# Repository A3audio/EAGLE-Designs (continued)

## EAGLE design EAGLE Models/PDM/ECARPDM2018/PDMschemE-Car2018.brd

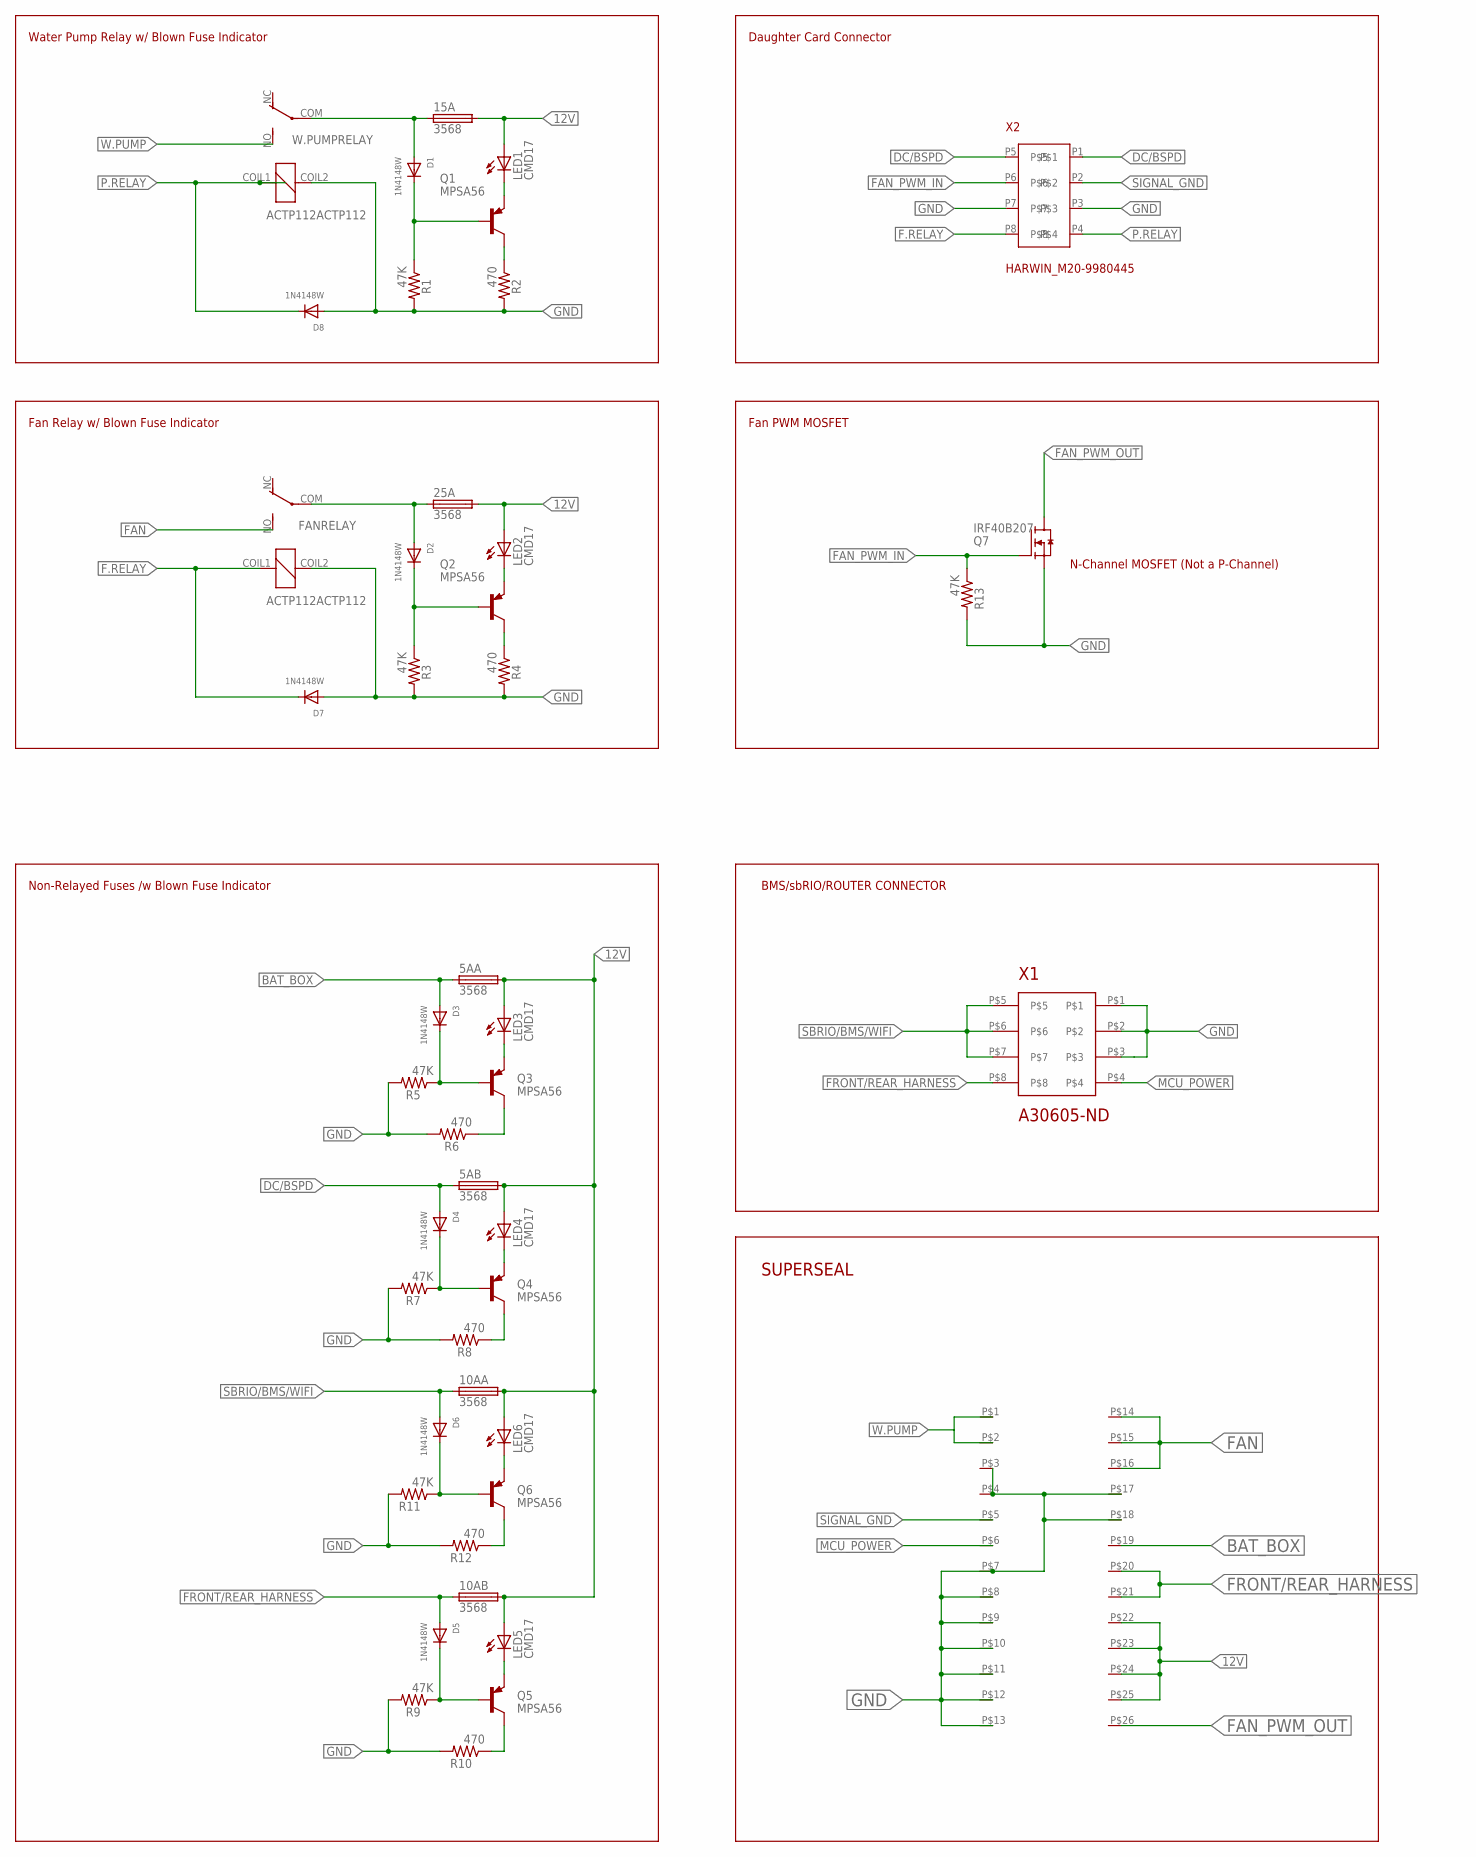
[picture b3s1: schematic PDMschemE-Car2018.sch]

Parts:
5AA, 5AB, 10AA, 10AB, 15A, 25A: 3568
D1, D2, D3, D4, D5, D6, D7, D8: 1N4148W; SOD-123
FANRELAY: ACTP112ACTP112; ACTP112
LED1, LED2, LED3, LED4, LED5, LED6: CMD17; CHIPLED_0805
Q1, Q2, Q3, Q4, Q5, Q6: MPSA56; TO92-CBE
Q7: IRF40B207; TO220-3
R1, R3, R5, R7, R9, R11, R13: 47K; R1206
R2, R4, R6, R8, R10, R12: 470; R1206
U$4: SUPERSEAL1.0_26POS_2ROW
W.PUMPRELAY: ACTP112ACTP112; ACTP112
X1: A30605-ND
X2: HARWIN_M20-9980445

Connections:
12V: 5AA.3 (2), 5AA.4 (2), 5AB.3 (2), 5AB.4 (2), 10AA.3 (2), 10AA.4 (2), 10AB.3 (2), 10AB.4 (2), 15A.3 (2), 15A.4 (2), 25A.3 (2), 25A.4 (2), LED1.A, LED2.A, LED3.A, LED4.A, LED5.A, LED6.A, U$4.P$22 (B22), U$4.P$23 (B23), U$4.P$24 (B24), U$4.P$25 (B25)
BAT_BOX: 5AA.1, 5AA.2 (1), D3.A, U$4.P$19 (B19)
DC/BSPD: 5AB.1, 5AB.2 (1), D4.A, X2.P1, X2.P5
F.RELAY: D7.C, FANRELAY.COIL1, X2.P8
FAN: FANRELAY.NO, U$4.P$14 (B14), U$4.P$15 (B15), U$4.P$16 (B16)
FAN_PWM_IN: Q7.G, R13.1, X2.P6
FAN_PWM_OUT: Q7.D, U$4.P$26 (B26)
FRONT/REAR_HARNESS: 10AB.1, 10AB.2 (1), D5.A, U$4.P$20 (B20), U$4.P$21 (B21), X1.P$8
GND: D7.A, D8.A, FANRELAY.COIL2, Q7.S, R1.2, R2.2, R3.2, R4.2, R5.2, R6.2, R7.2, R8.2, R9.2, R10.2, R11.2, R12.2, R13.2, U$4.P$3 (B3), U$4.P$4 (B4), U$4.P$7 (B7), U$4.P$8 (B8), U$4.P$9 (B9), U$4.P$10 (B10), U$4.P$11 (B11), U$4.P$12 (B12), U$4.P$13 (B13), U$4.P$17 (B17), U$4.P$18 (B18), W.PUMPRELAY.COIL2, X1.P$1, X1.P$2, X1.P$3, X2.P3, X2.P7
MCU_POWER: U$4.P$6 (B6), X1.P$4
unnamed: LED1.C, Q1.E
unnamed: Q3.C, R6.1
unnamed: LED3.C, Q3.E
unnamed: 25A.1, 25A.2 (1), D2.A, FANRELAY.COM
unnamed: Q1.C, R2.1
unnamed: D1.C, Q1.B, R1.1
unnamed: D2.C, Q2.B, R3.1
unnamed: 15A.1, 15A.2 (1), D1.A, W.PUMPRELAY.COM
unnamed: Q2.C, R4.1
unnamed: LED2.C, Q2.E
unnamed: D3.C, Q3.B, R5.1
unnamed: LED4.C, Q4.E
unnamed: D4.C, Q4.B, R7.1
unnamed: Q4.C, R8.1
unnamed: LED6.C, Q6.E
unnamed: D6.C, Q6.B, R11.1
unnamed: Q6.C, R12.1
unnamed: LED5.C, Q5.E
unnamed: D5.C, Q5.B, R9.1
unnamed: Q5.C, R10.1
P.RELAY: D8.C, W.PUMPRELAY.COIL1, X2.P4
SBRIO/BMS/WIFI: 10AA.1, 10AA.2 (1), D6.A, X1.P$5, X1.P$6, X1.P$7
SIGNAL_GND: U$4.P$5 (B5), X2.P2
W.PUMP: U$4.P$1 (B1), U$4.P$2 (B2), W.PUMPRELAY.NO

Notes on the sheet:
Water Pump Relay w/ Blown Fuse Indicator
Fan Relay w/ Blown Fuse Indicator
Non-Relayed Fuses /w Blown Fuse Indicator
Fan PWM MOSFET
N-Channel MOSFET (Not a P-Channel)
Daughter Card Connector
BMS/sbRIO/ROUTER CONNECTOR
SUPERSEAL

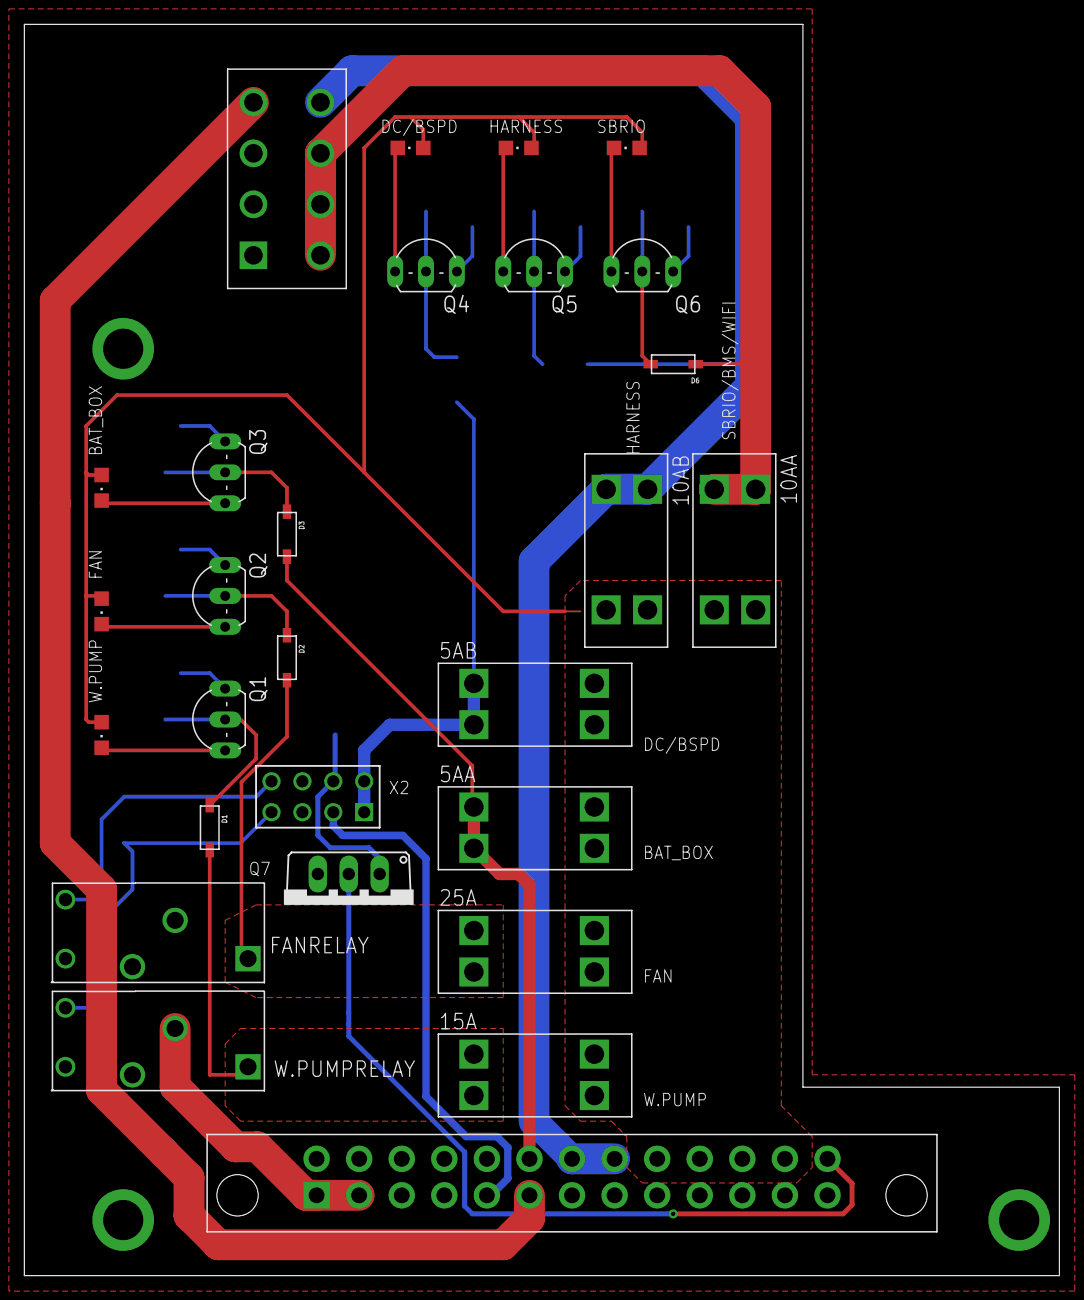
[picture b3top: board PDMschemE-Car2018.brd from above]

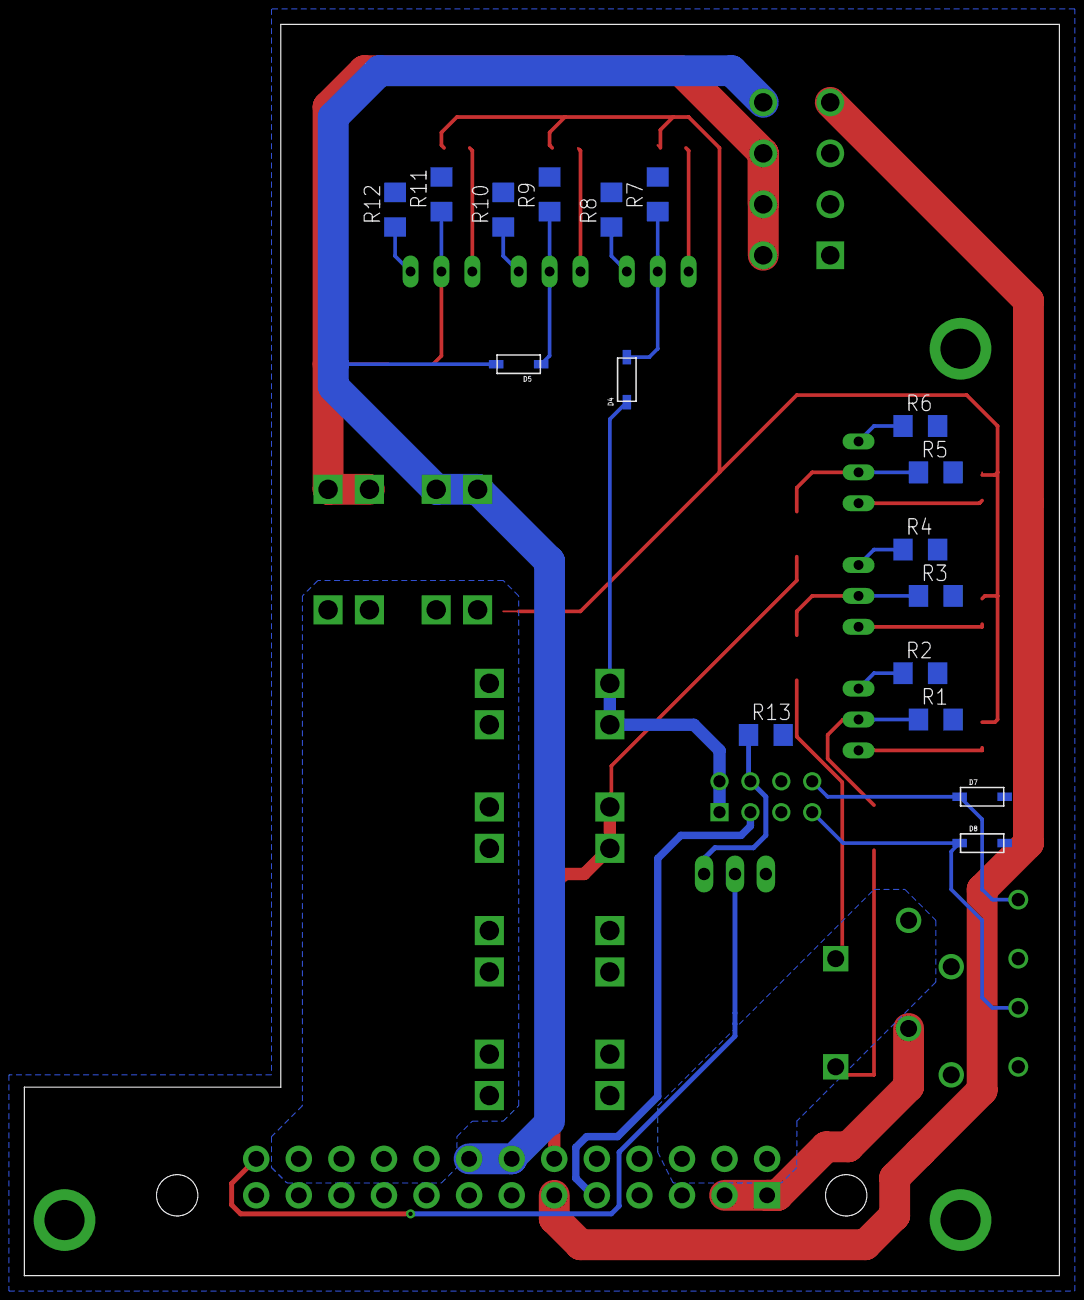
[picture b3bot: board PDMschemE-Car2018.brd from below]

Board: 2 copper layers, 85.1 x 102.9 mm, 45 parts (17 on the bottom side), 34 nets.

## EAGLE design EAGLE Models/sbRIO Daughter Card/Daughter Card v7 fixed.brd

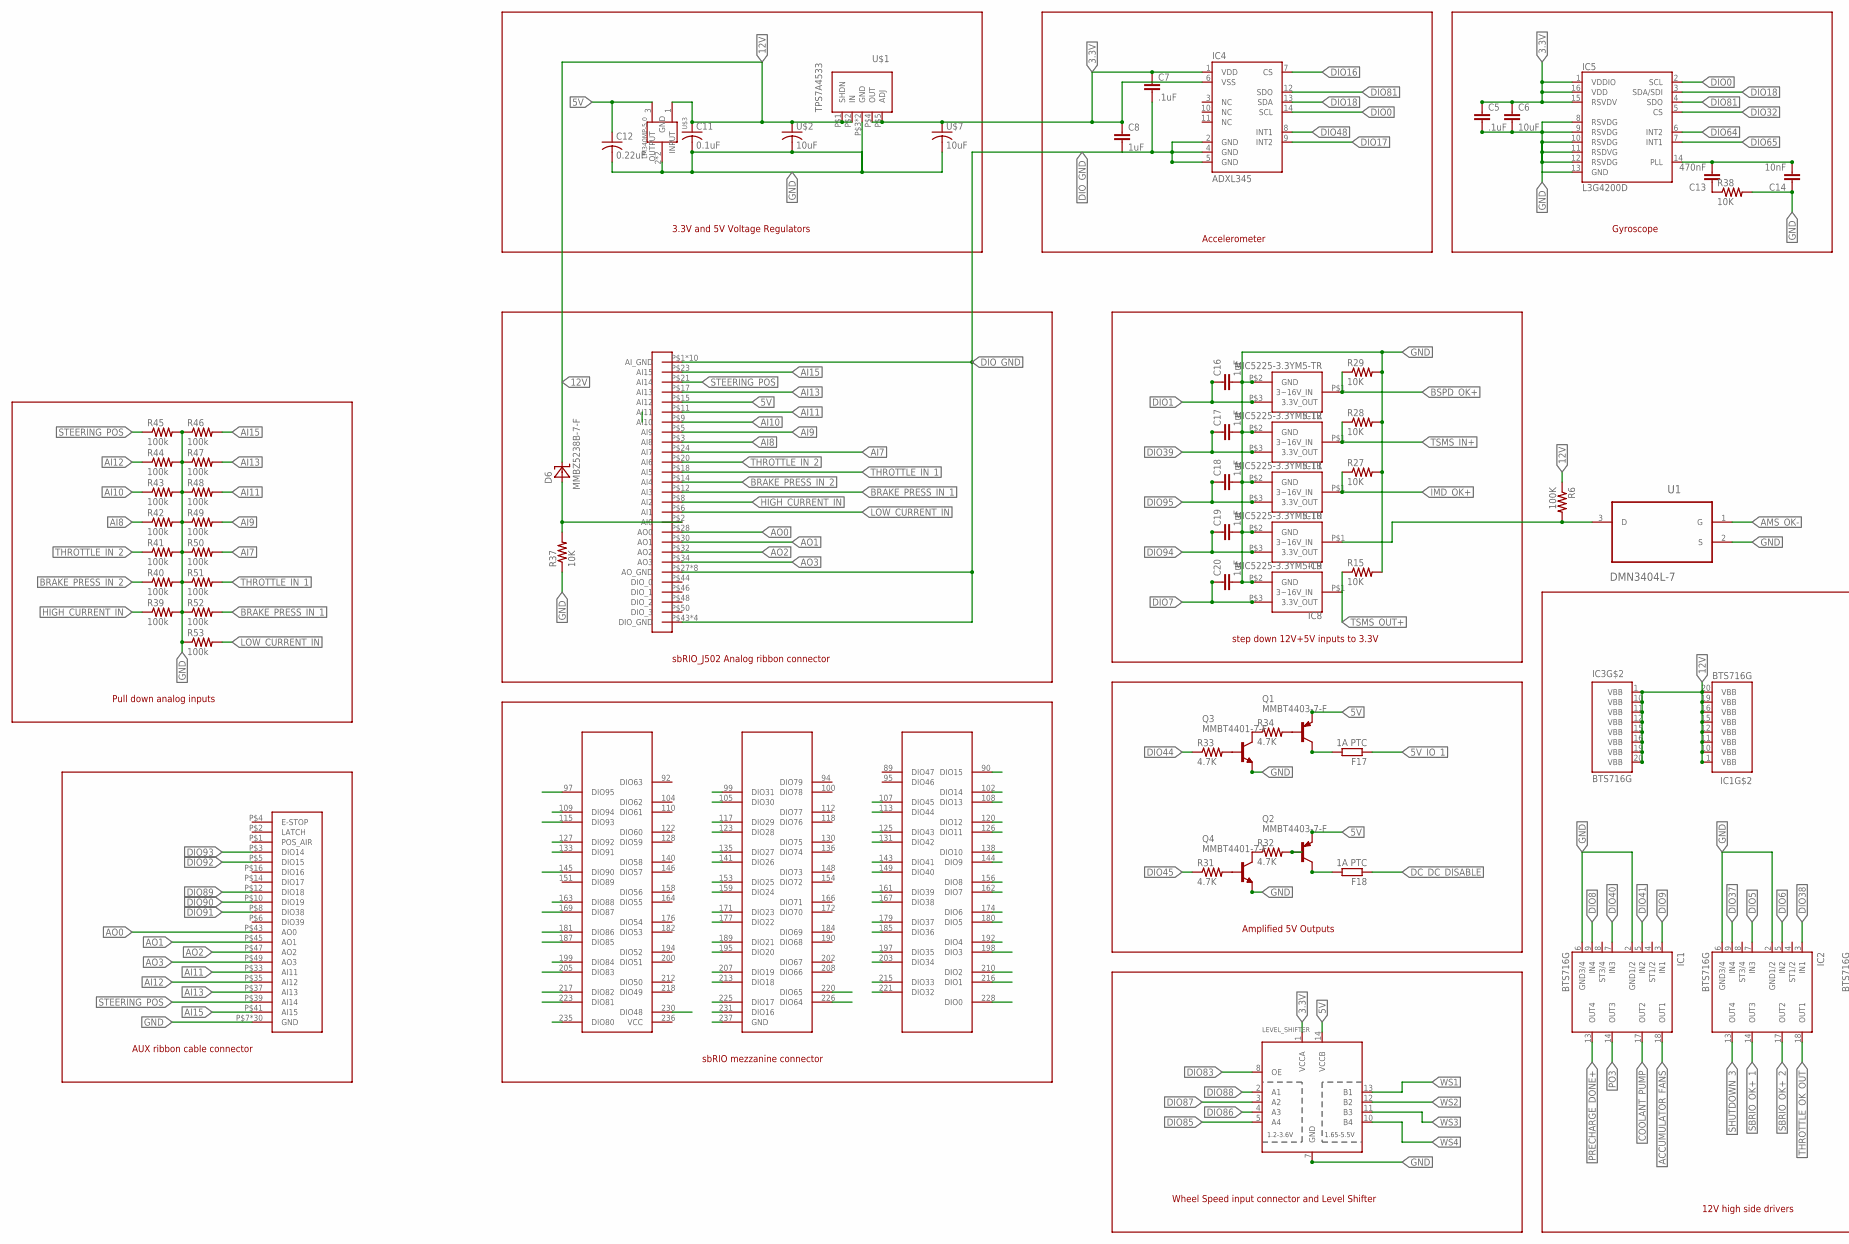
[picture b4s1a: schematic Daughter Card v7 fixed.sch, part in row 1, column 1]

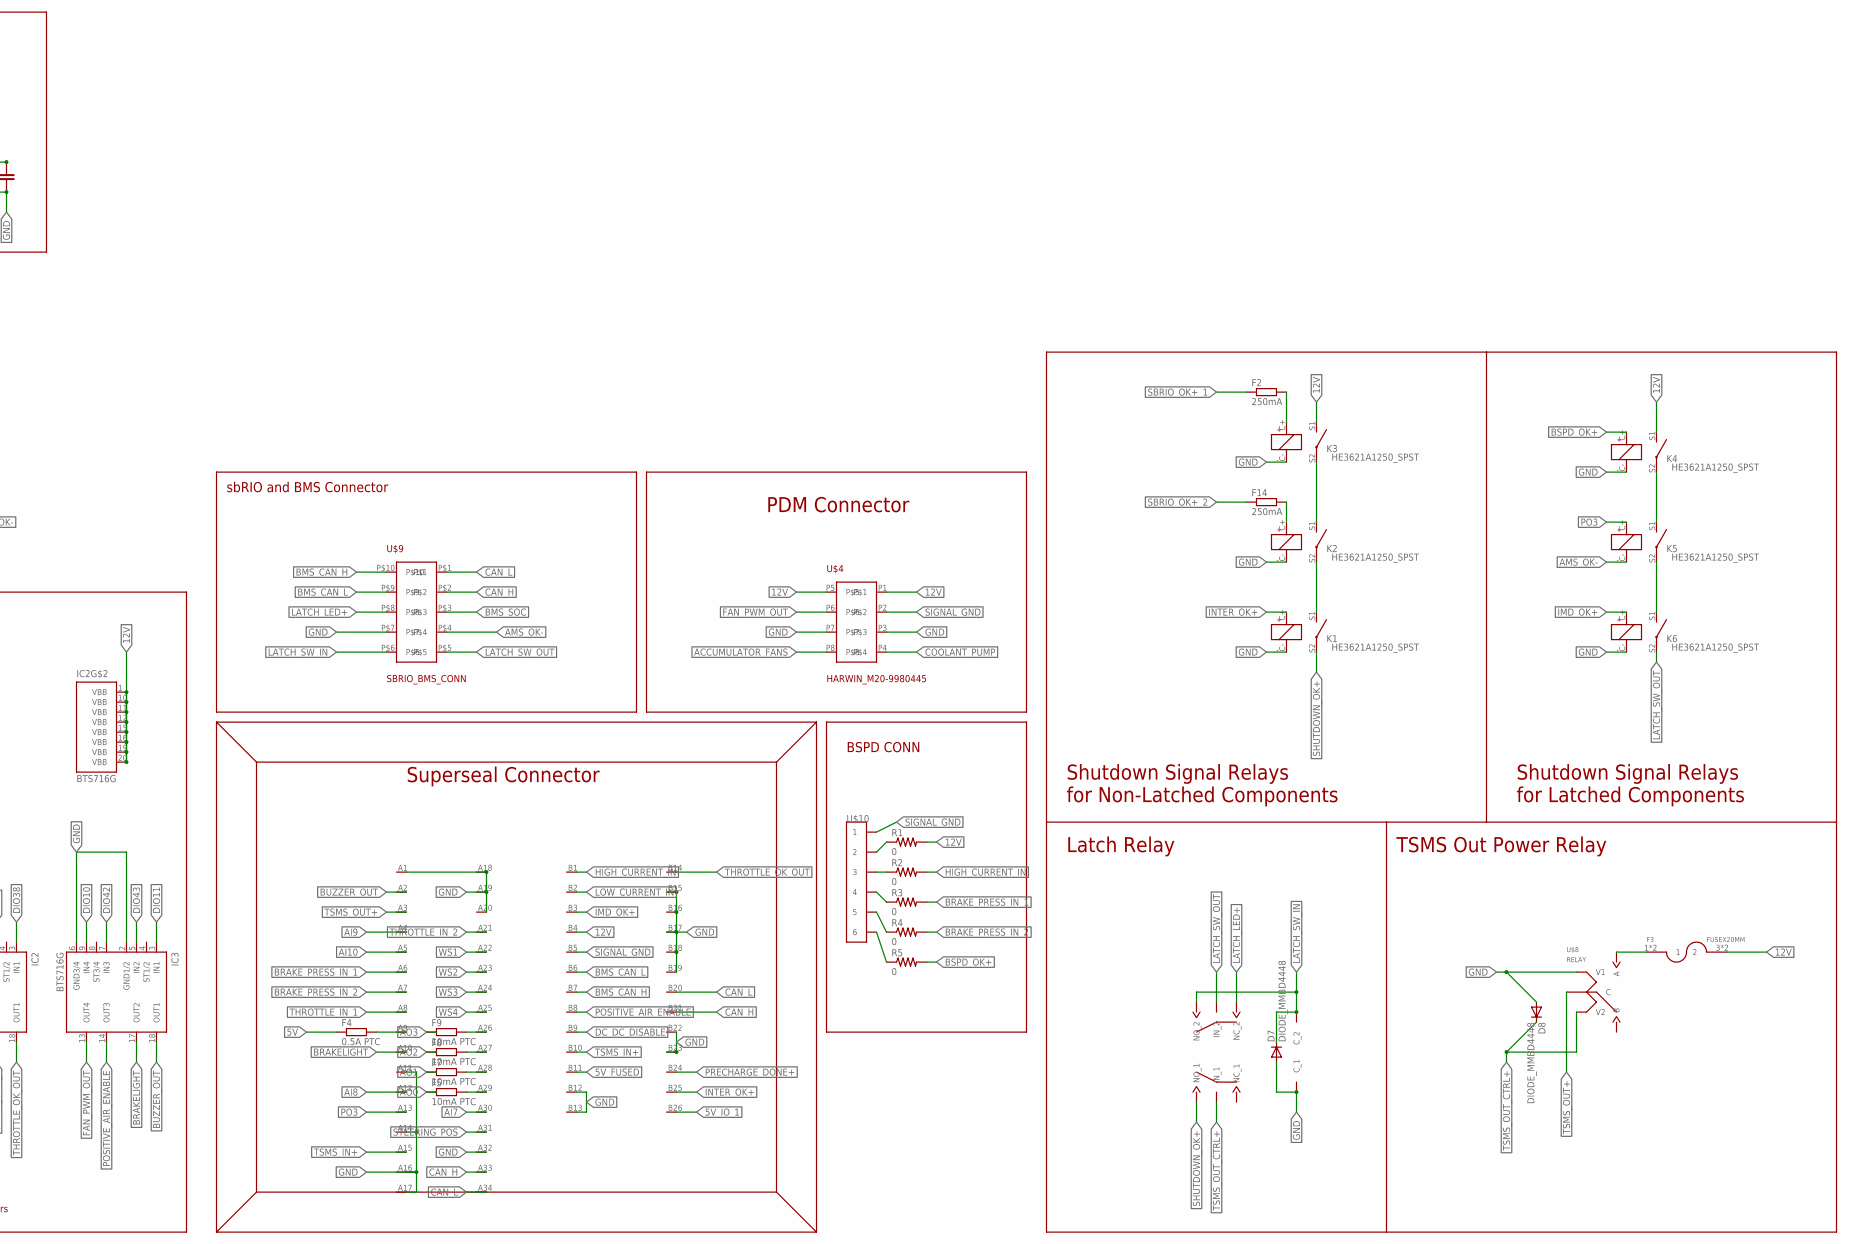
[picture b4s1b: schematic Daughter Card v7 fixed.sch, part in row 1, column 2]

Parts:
C5, C7: .1uF; 0603-CAP
C6: 10uF; 0603-CAP
C8, C16, C17, C18, C19, C20: 1uF; 0603-CAP
C11: 0.1uF; C1206
C12: 0.22uF; C1206
C13: 470nF; 0603-CAP
C14: 10nF; 0603-CAP
D6: MMBZ5238B-7-F; SOT-23-3
D7, D8: DIODE_MMBD4448; SOT-23-3
F2, F14: 250mA; R0603
F3: FUSEX20MM; FUSE_5MM
F4: 0.5A PTC; R0603
F5, F7, F8, F9: 10mA PTC; R0603
F17, F18: 1A PTC; R0603
IC1, IC2, IC3: BTS716G; PG-DSO-20
IC4: ADXL345; LGA14
IC5: L3G4200D; LGA16-4X4
IC8, IC9, IC10, IC11, IC12: MIC5225-3.3YM5-TR; SOT-23-3
K1, K2, K3, K4, K5, K6: HE3621A1250_SPST
LATCH_U7: JW2SN-DC12V; DPDT_JW2_FORM_C
LEVEL_SHIFTER: TXB0104PWR; TSSOP14
Q1, Q2: MMBT4403-7-F; SOT-23-3
Q3, Q4: MMBT4401-7-F; SOT-23-3
R1, R2, R3, R4, R5: 0; M0805
R6: 100K; R0603
R15, R27, R28, R29, R37, R38: 10K; R0603
R31, R32, R33, R34: 4.7K; R0603
R39, R40, R41, R42, R43, R44, R45, R46, R47, R48, R49, R50, R51, R52, R53: 100k; R0603
SBRIO_ANALOG: SBRIO_MIO; SBRIO_J502_J503
SBRIO_AUX: SBRIO_AUX; SBRIO_J502_J503
SBRIO_MEZZANINE: SBRIO_RMC; SEAM-40-XX.X-XX-06-X-A
U1: DMN3404L-7; SOT95P235X112-3N
U$1: TPS7A4533; DIGIKEY_P-N 490-12344-1-ND
U$2, U$7: 10uF; C1206
U$3: LM340MP-5.0; SOT-223-4
U$4: HARWIN_M20-9980445
U$6: SUPERSEAL1.0_60POS
U$8: RELAY
U$9: SBRIO_BMS_CONN; SBRIO_W
U$10: SULLINS_1MM_6P_HEADER; SULLINS_1MM_HEADER

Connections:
3.3V: C5.1, C6.1, C7.1, C8.1, IC4.1 (VDD), IC4.6 (VSS), IC5.1 (VDDIO), IC5.15 (RSVDV), IC5.16 (VDD), LEVEL_SHIFTER.1 (VCCA), U$1.P$4 (OUT), U$1.P$5 (ADJ), U$7.1
5V: C12.1, F4.1, LEVEL_SHIFTER.14 (VCCB), Q1.P$3 (E), Q2.P$3 (E), SBRIO_ANALOG.P$15 (AI12), U$3.3 (OUTPUT)
5V_FUSED: F4.2, U$6.A9, U$6.B11
5V_IO_1: F17.1, U$6.B26
12V: C11.1, D6.P$1 (C), F3.3 (2), F3.4 (2), IC1.1 (VBB), IC1.10 (VBB), IC1.11 (VBB), IC1.12 (VBB), IC1.15 (VBB), IC1.16 (VBB), IC1.19 (VBB), IC1.20 (VBB), IC2.1 (VBB), IC2.10 (VBB), IC2.11 (VBB), IC2.12 (VBB), IC2.15 (VBB), IC2.16 (VBB), IC2.19 (VBB), IC2.20 (VBB), IC3.1 (VBB), IC3.10 (VBB), IC3.11 (VBB), IC3.12 (VBB), IC3.15 (VBB), IC3.16 (VBB), IC3.19 (VBB), IC3.20 (VBB), K3.S1 (SW_1), K4.S1 (SW_1), R1.2, R6.1, U$1.P$1 (SHDN), U$1.P$2 (IN), U$2.1, U$3.1 (INPUT), U$4.P1, U$4.P5, U$6.B4
ACCUMULATOR_FANS: IC1.18 (OUT1), U$4.P8
AI7: R50.2, SBRIO_ANALOG.P$24 (AI7), U$6.A30
AI8: R42.1, SBRIO_ANALOG.P$3 (AI8), U$6.A12
AI9: R49.2, SBRIO_ANALOG.P$5 (AI9), U$6.A4
AI10: R43.1, SBRIO_ANALOG.P$9 (AI10), U$6.A5
AI11: R48.2, SBRIO_ANALOG.P$11 (AI11), SBRIO_AUX.P$33 (AI11)
AI12: R44.1, SBRIO_AUX.P$35 (AI12)
AI13: R47.2, SBRIO_ANALOG.P$17 (AI13), SBRIO_AUX.P$37 (AI13)
AI15: R46.2, SBRIO_ANALOG.P$23 (AI15), SBRIO_AUX.P$41 (AI15)
AMS_OK-: K5.C-, U1.1 (G), U$9.P$4
AO0: F5.1, SBRIO_ANALOG.P$28 (AO0), SBRIO_AUX.P$43 (AO0)
AO1: F7.1, SBRIO_ANALOG.P$30 (AO1), SBRIO_AUX.P$45 (AO1)
AO2: F8.1, SBRIO_ANALOG.P$32 (AO2), SBRIO_AUX.P$47 (AO2)
AO3: F9.1, SBRIO_ANALOG.P$34 (AO3), SBRIO_AUX.P$49 (AO3)
BMS_CAN_H: U$6.B7, U$9.P$10
BMS_CAN_L: U$6.B6, U$9.P$9
BMS_SOC: U$9.P$3
BRAKELIGHT: IC3.17 (OUT2), U$6.A10
BRAKE_PRESS_IN_1: R3.2, R52.2, SBRIO_ANALOG.P$12 (AI3), U$6.A6
BRAKE_PRESS_IN_2: R4.2, R40.1, SBRIO_ANALOG.P$14 (AI4), U$6.A7
BSPD_OK+: IC12.P$1 (3~16V_IN), K4.C+, R5.2, R29.1
BUZZER_OUT: IC3.18 (OUT1), U$6.A2
CAN_H: U$6.A33, U$6.B21, U$9.P$2
CAN_L: U$6.A34, U$6.B20, U$9.P$1
COOLANT_PUMP: IC1.17 (OUT2), U$4.P4
DC_DC_DISABLE: F18.1, U$6.B9
DIO0: IC4.14 (SCL), IC5.2 (SCL), SBRIO_MEZZANINE.228 (DIO0)
DIO1: C16.1, IC12.P$3 (3.3V_OUT), SBRIO_MEZZANINE.216 (DIO1)
DIO2: SBRIO_MEZZANINE.210 (DIO2)
DIO3: SBRIO_MEZZANINE.198 (DIO3)
DIO4: SBRIO_MEZZANINE.192 (DIO4)
DIO5: IC2.7 (IN3), SBRIO_MEZZANINE.180 (DIO5)
DIO6: IC2.5 (IN2), SBRIO_MEZZANINE.174 (DIO6)
DIO7: C20.1, IC8.P$3 (3.3V_OUT), SBRIO_MEZZANINE.162 (DIO7)
DIO8: IC1.9 (IN4), SBRIO_MEZZANINE.156 (DIO8)
DIO9: IC1.3 (IN1), SBRIO_MEZZANINE.144 (DIO9)
DIO10: IC3.9 (IN4), SBRIO_MEZZANINE.138 (DIO10)
DIO11: IC3.3 (IN1), SBRIO_MEZZANINE.126 (DIO11)
DIO12: SBRIO_MEZZANINE.120 (DIO12)
DIO13: SBRIO_MEZZANINE.108 (DIO13)
DIO14: SBRIO_MEZZANINE.102 (DIO14)
DIO15: SBRIO_MEZZANINE.90 (DIO15)
DIO16: IC4.7 (CS), SBRIO_MEZZANINE.231 (DIO16)
DIO17: IC4.9 (INT2), SBRIO_MEZZANINE.225 (DIO17)
DIO18: IC4.13 (SDA), IC5.3 (SDA/SDI), SBRIO_MEZZANINE.213 (DIO18)
DIO19: SBRIO_MEZZANINE.207 (DIO19)
DIO20: SBRIO_MEZZANINE.195 (DIO20)
DIO21: SBRIO_MEZZANINE.189 (DIO21)
DIO22: SBRIO_MEZZANINE.177 (DIO22)
DIO23: SBRIO_MEZZANINE.171 (DIO23)
DIO24: SBRIO_MEZZANINE.159 (DIO24)
DIO25: SBRIO_MEZZANINE.153 (DIO25)
DIO26: SBRIO_MEZZANINE.141 (DIO26)
DIO27: SBRIO_MEZZANINE.135 (DIO27)
DIO28: SBRIO_MEZZANINE.123 (DIO28)
DIO29: SBRIO_MEZZANINE.117 (DIO29)
DIO30: SBRIO_MEZZANINE.105 (DIO30)
DIO31: SBRIO_MEZZANINE.99 (DIO31)
DIO32: IC5.5 (CS), SBRIO_MEZZANINE.221 (DIO32)
DIO33: SBRIO_MEZZANINE.215 (DIO33)
DIO34: SBRIO_MEZZANINE.203 (DIO34)
DIO35: SBRIO_MEZZANINE.197 (DIO35)
DIO36: SBRIO_MEZZANINE.185 (DIO36)
DIO37: IC2.9 (IN4), SBRIO_MEZZANINE.179 (DIO37)
DIO38: IC2.3 (IN1), SBRIO_MEZZANINE.167 (DIO38)
DIO39: C17.1, IC11.P$3 (3.3V_OUT), SBRIO_MEZZANINE.161 (DIO39)
DIO40: IC1.7 (IN3), SBRIO_MEZZANINE.149 (DIO40)
DIO41: IC1.5 (IN2), SBRIO_MEZZANINE.143 (DIO41)
DIO42: IC3.7 (IN3), SBRIO_MEZZANINE.131 (DIO42)
DIO43: IC3.5 (IN2), SBRIO_MEZZANINE.125 (DIO43)
DIO44: R33.1, SBRIO_MEZZANINE.113 (DIO44)
DIO45: R31.1, SBRIO_MEZZANINE.107 (DIO45)
DIO48: IC4.8 (INT1), SBRIO_MEZZANINE.230 (DIO48)
DIO64: IC5.6 (INT2), SBRIO_MEZZANINE.226 (DIO64)
DIO65: IC5.7 (INT1), SBRIO_MEZZANINE.220 (DIO65)
DIO80: SBRIO_MEZZANINE.235 (DIO80)
DIO81: IC4.12 (SDO), IC5.4 (SDO), SBRIO_MEZZANINE.223 (DIO81)
DIO82: SBRIO_MEZZANINE.217 (DIO82)
DIO83: LEVEL_SHIFTER.8 (OE), SBRIO_MEZZANINE.205 (DIO83)
DIO84: SBRIO_MEZZANINE.199 (DIO84)
DIO85: LEVEL_SHIFTER.5 (A4), SBRIO_MEZZANINE.187 (DIO85)
DIO86: LEVEL_SHIFTER.4 (A3), SBRIO_MEZZANINE.181 (DIO86)
DIO87: LEVEL_SHIFTER.3 (A2), SBRIO_MEZZANINE.169 (DIO87)
DIO88: LEVEL_SHIFTER.2 (A1), SBRIO_MEZZANINE.163 (DIO88)
DIO89: SBRIO_AUX.P$12 (DIO18)
DIO90: SBRIO_AUX.P$10 (DIO19), SBRIO_MEZZANINE.145 (DIO90)
DIO91: SBRIO_AUX.P$8 (DIO38), SBRIO_MEZZANINE.133 (DIO91)
DIO92: SBRIO_AUX.P$5 (DIO15), SBRIO_MEZZANINE.127 (DIO92)
DIO93: SBRIO_AUX.P$3 (DIO14), SBRIO_MEZZANINE.115 (DIO93)
DIO94: C19.1, IC9.P$3 (3.3V_OUT), SBRIO_MEZZANINE.109 (DIO94)
DIO95: C18.1, IC10.P$3 (3.3V_OUT), SBRIO_MEZZANINE.97 (DIO95)
DIO_GND: C7.2, C8.2, IC4.2 (GND), IC4.4 (GND), IC4.5 (GND), SBRIO_ANALOG.P$1 (AI_GND), SBRIO_ANALOG.P$4 (AI_GND), SBRIO_ANALOG.P$7 (AI_GND), SBRIO_ANALOG.P$10 (AI_GND), SBRIO_ANALOG.P$13 (AI_GND), SBRIO_ANALOG.P$16 (AI_GND), SBRIO_ANALOG.P$19 (AI_GND), SBRIO_ANALOG.P$22 (AI_GND), SBRIO_ANALOG.P$25 (AI_GND), SBRIO_ANALOG.P$26 (AI_GND), SBRIO_ANALOG.P$27 (AO_GND), SBRIO_ANALOG.P$29 (AO_GND), SBRIO_ANALOG.P$31 (AO_GND), SBRIO_ANALOG.P$33 (AO_GND), SBRIO_ANALOG.P$35 (AO_GND), SBRIO_ANALOG.P$37 (AO_GND), SBRIO_ANALOG.P$39 (AO_GND), SBRIO_ANALOG.P$41 (AO_GND), SBRIO_ANALOG.P$43 (DIO_GND), SBRIO_ANALOG.P$45 (DIO_GND), SBRIO_ANALOG.P$47 (DIO_GND), SBRIO_ANALOG.P$49 (DIO_GND)
FAN_PWM_OUT: IC3.13 (OUT4), U$4.P6
GND: C5.2, C6.2, C11.2, C12.2, C14.1, C16.2, C17.2, C18.2, C19.2, C20.2, D7.P$2 (A), D8.P$2 (A), IC1.2 (GND1/2), IC1.6 (GND3/4), IC2.2 (GND1/2), IC2.6 (GND3/4), IC3.2 (GND1/2), IC3.6 (GND3/4), IC5.8 (RSVDG), IC5.9 (RSVDG), IC5.10 (RSVDG), IC5.11 (RSDVG), IC5.12 (RSVDG), IC5.13 (GND), IC8.P$2 (GND), IC9.P$2 (GND), IC10.P$2 (GND), IC11.P$2 (GND), IC12.P$2 (GND), K1.C-, K2.C-, K3.C-, K4.C-, K6.C-, LATCH_U7.COIL_1 (C_1), LEVEL_SHIFTER.7 (GND), Q3.P$3 (E), Q4.P$3 (E), R15.2, R27.2, R28.2, R29.2, R37.1, R38.2, R39.2, R40.2, R41.2, R42.2, R43.2, R44.2, R45.2, R46.1, R47.1, R48.1, R49.1, R50.1, R51.1, R52.1, R53.1, SBRIO_AUX.P$7 (GND), SBRIO_AUX.P$9 (GND), SBRIO_AUX.P$11 (GND), SBRIO_AUX.P$13 (GND), SBRIO_AUX.P$15 (GND), SBRIO_AUX.P$17 (GND), SBRIO_AUX.P$18 (GND), SBRIO_AUX.P$19 (GND), SBRIO_AUX.P$20 (GND), SBRIO_AUX.P$21 (GND), SBRIO_AUX.P$22 (GND), SBRIO_AUX.P$23 (GND), SBRIO_AUX.P$24 (GND), SBRIO_AUX.P$25 (GND), SBRIO_AUX.P$26 (GND), SBRIO_AUX.P$27 (GND), SBRIO_AUX.P$28 (GND), SBRIO_AUX.P$29 (GND), SBRIO_AUX.P$30 (GND), SBRIO_AUX.P$31 (GND), SBRIO_AUX.P$32 (GND), SBRIO_AUX.P$34 (GND), SBRIO_AUX.P$36 (GND), SBRIO_AUX.P$38 (GND), SBRIO_AUX.P$40 (GND), SBRIO_AUX.P$42 (GND), SBRIO_AUX.P$44 (GND), SBRIO_AUX.P$46 (GND), SBRIO_AUX.P$48 (GND), SBRIO_AUX.P$50 (GND), SBRIO_MEZZANINE.237 (GND), U1.2 (S), U$1.P$3 (GND), U$1.P$6 (GND), U$2.2, U$3.2 (GND), U$3.4 (GND), U$4.P3, U$4.P7, U$6.A1, U$6.A11, U$6.A14, U$6.A16, U$6.A17, U$6.A18, U$6.A19, U$6.A20, U$6.A32, U$6.B12, U$6.B13, U$6.B15, U$6.B16, U$6.B17, U$6.B18, U$6.B19, U$6.B22, U$6.B23, U$7.2, U$8.V1, U$9.P$7
HIGH_CURRENT_IN: R2.2, R39.1, SBRIO_ANALOG.P$8 (AI2), U$6.B1
IMD_OK+: IC10.P$1 (3~16V_IN), K6.C+, R27.1, U$6.B3
INTER_OK+: K1.C+, U$6.B25
K4: K4.S2 (SW_2), K5.S1 (SW_1)
LATCH_LED+: LATCH_U7.NC_2, U$9.P$8
LATCH_SW_IN: D7.P$1 (C), LATCH_U7.COIL_2 (C_2), LATCH_U7.NO_2, U$9.P$6
LATCH_SW_OUT: K6.S2 (SW_2), LATCH_U7.CENTER_2 (IN_2), U$9.P$5
LOW_CURRENT_IN: R53.2, SBRIO_ANALOG.P$6 (AI1), U$6.B2
unnamed: K2.S1 (SW_1), K3.S2 (SW_2)
unnamed: F5.2, U$6.A29
unnamed: D6.P$2 (A), R37.2, SBRIO_ANALOG.P$2 (AI0)
unnamed: Q1.P$2 (B), R34.2
unnamed: F7.2, U$6.A28
unnamed: K1.S1 (SW_1), K2.S2 (SW_2)
unnamed: Q3.P$1 (C), R34.1
unnamed: F8.2, U$6.A27
unnamed: F9.2, U$6.A26
unnamed: C13.1, R38.1
unnamed: R1.1, U$10.P2 (2)
unnamed: K5.S2 (SW_2), K6.S1 (SW_1)
unnamed: F3.1, F3.2 (1), U$8.A
unnamed: R2.1, U$10.P3 (3)
unnamed: R3.1, U$10.P4 (4)
unnamed: R4.1, U$10.P5 (5)
unnamed: Q4.P$1 (C), R32.1
unnamed: Q4.P$2 (B), R31.2
unnamed: R5.1, U$10.P6 (6)
unnamed: Q3.P$2 (B), R33.2
unnamed: IC9.P$1 (3~16V_IN), R6.2, U1.3 (D)
unnamed: C13.2, C14.2, IC5.14 (PLL)
unnamed: F17.2, Q1.P$1 (C)
unnamed: F18.2, Q2.P$1 (C)
unnamed: Q2.P$2 (B), R32.2
PO3: IC1.14 (OUT3), K5.C+, U$6.A13
POSITIVE_AIR_ENABLE: IC3.14 (OUT3), U$6.B8
PRECHARGE_DONE+: IC1.13 (OUT4), U$6.B24
SBRIO_OK+_1: F2.1, IC2.14 (OUT3)
SBRIO_OK+_1_RELAY_IN: F2.2, K3.C+
SBRIO_OK+_2: F14.1, IC2.17 (OUT2)
SBRIO_OK_2_RELAY: F14.2, K2.C+
SHUTDOWN_3: IC2.13 (OUT4)
SHUTDOWN_OK+: K1.S2 (SW_2), LATCH_U7.NO_1
SIGNAL_GND: U$4.P2, U$6.B5, U$10.P1 (1)
STEERING_POS: R45.1, SBRIO_ANALOG.P$21 (AI14), SBRIO_AUX.P$39 (AI14), U$6.A31
THROTTLE_IN_1: R51.2, SBRIO_ANALOG.P$18 (AI5), U$6.A8
THROTTLE_IN_2: R41.1, SBRIO_ANALOG.P$20 (AI6), U$6.A21
THROTTLE_OK_OUT: IC2.18 (OUT1), U$6.B14
TSMS_IN+: IC11.P$1 (3~16V_IN), R28.1, U$6.A15, U$6.B10
TSMS_OUT+: IC8.P$1 (3~16V_IN), R15.1, U$6.A3, U$8.CENTER (C)
TSMS_OUT_CTRL+: D8.P$1 (C), LATCH_U7.CENTER_1 (IN_1), U$8.V2
VCC: SBRIO_MEZZANINE.236 (VCC)
WS1: LEVEL_SHIFTER.13 (B1), U$6.A22
WS2: LEVEL_SHIFTER.12 (B2), U$6.A23
WS3: LEVEL_SHIFTER.11 (B3), U$6.A24
WS4: LEVEL_SHIFTER.10 (B4), U$6.A25

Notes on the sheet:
step down 12V+5V inputs to 3.3V
AUX ribbon cable connector
Amplified 5V Outputs
sbRIO mezzanine connector
sbRIO_J502 Analog ribbon connector
Gyroscope
3.3V and 5V Voltage Regulators
Accelerometer
Wheel Speed input connector and Level Shifter
12V high side drivers
Pull down analog inputs
Shutdown Signal Relays for Non-Latched Components
Shutdown Signal Relays for Latched Components
Latch Relay
TSMS Out Power Relay
BSPD CONN
sbRIO and BMS Connector
Superseal Connector
PDM Connector

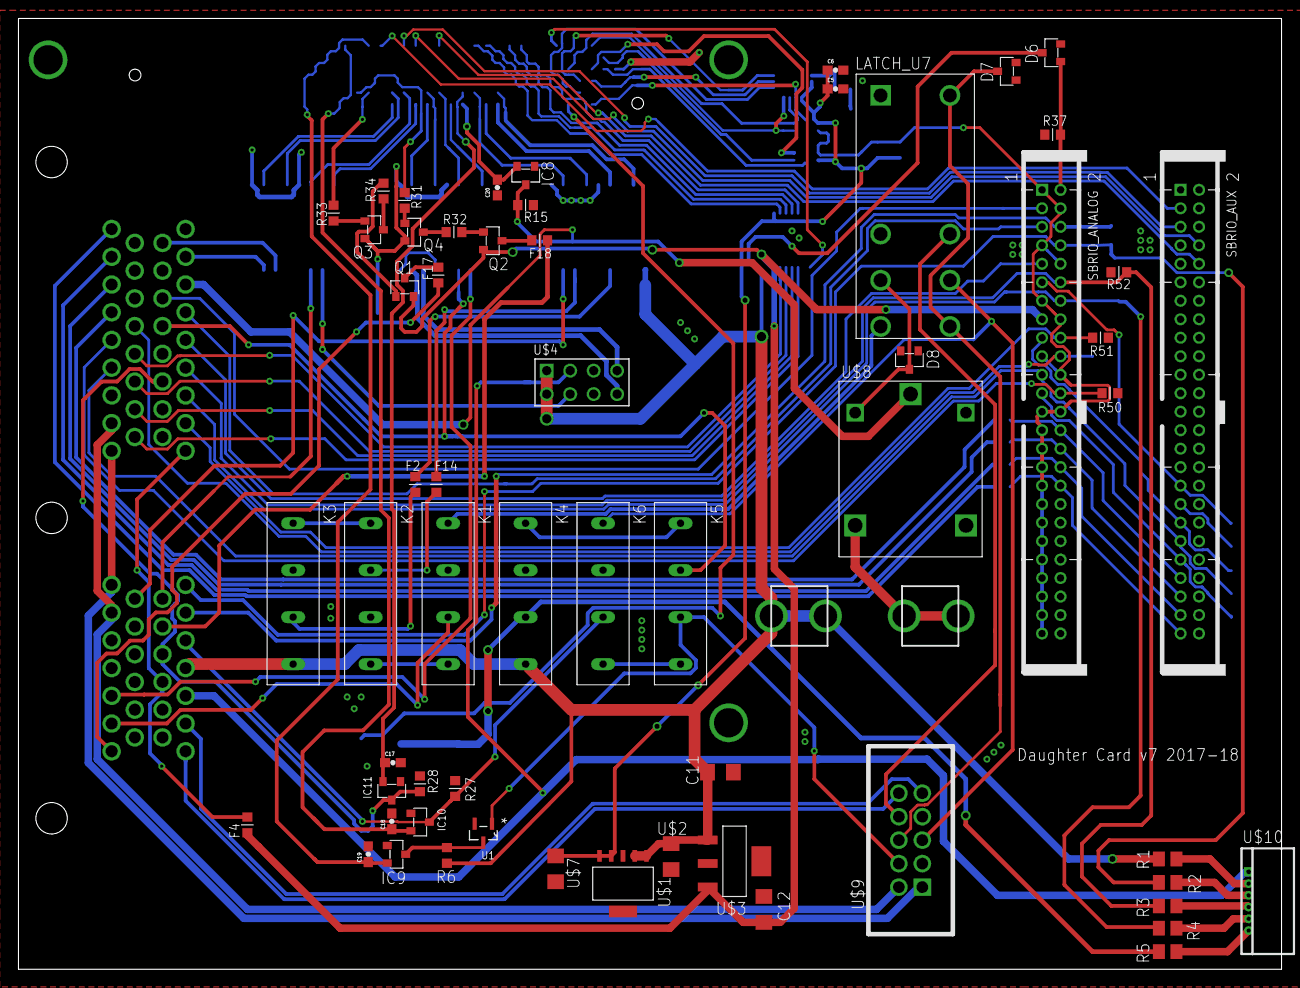
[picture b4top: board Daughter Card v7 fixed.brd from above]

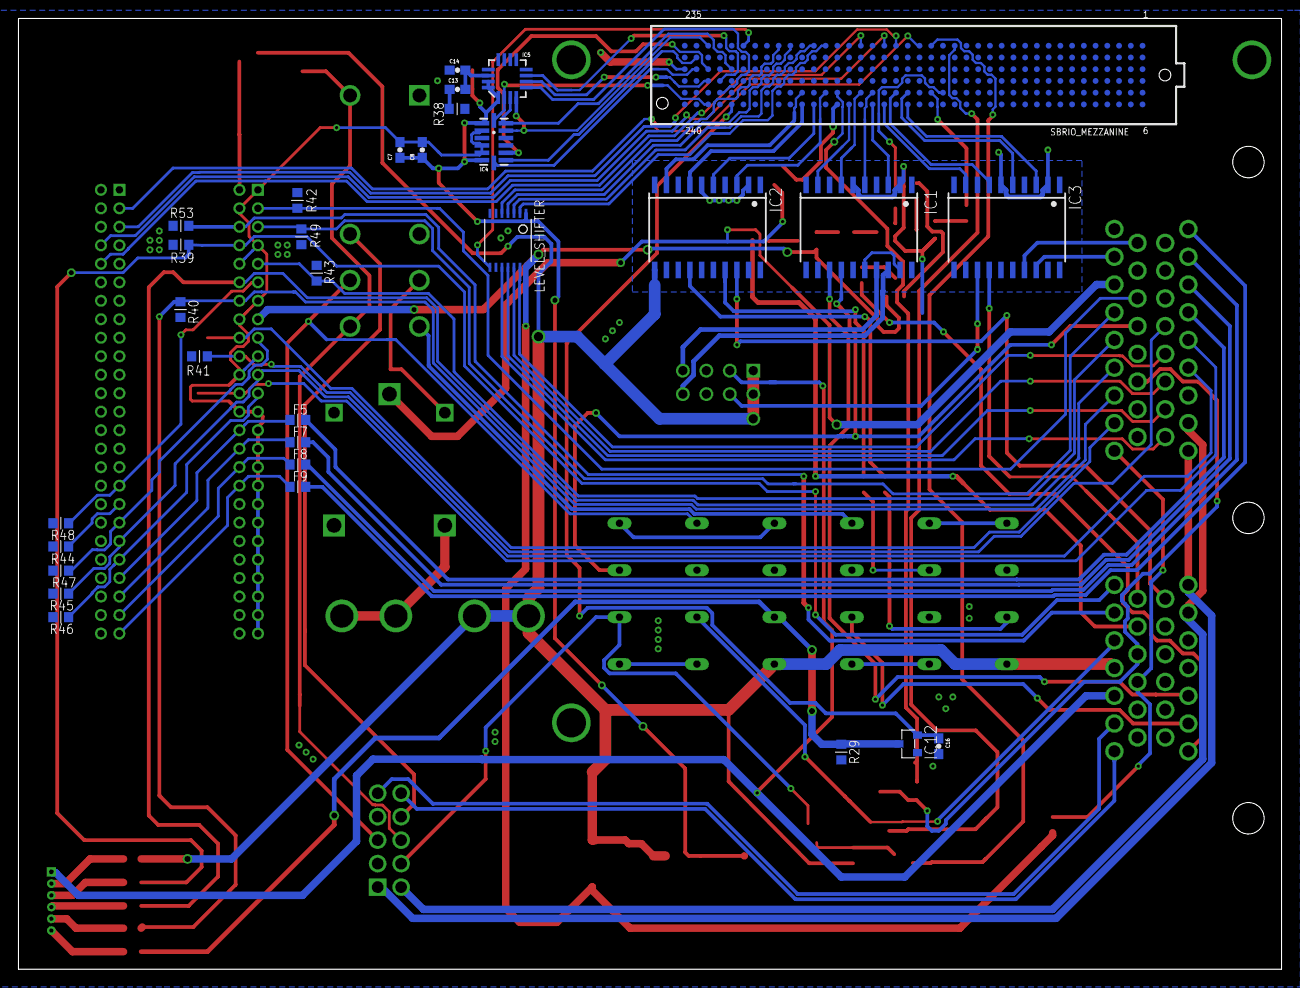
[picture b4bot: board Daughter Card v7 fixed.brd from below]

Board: 2 copper layers, 136.7 x 102.9 mm, 92 parts (31 on the bottom side), 123 nets.

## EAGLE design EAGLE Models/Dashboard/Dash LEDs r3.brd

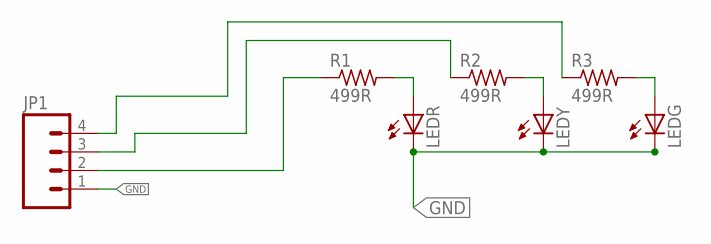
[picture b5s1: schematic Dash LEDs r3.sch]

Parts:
JP1: M04PTH; 1X04
LEDG: LED5MM
LEDR: LED5MM
LEDY: LED5MM
R1, R2, R3: 499R; R0805

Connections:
DRV1: JP1.2, R1.1
DRV2: JP1.3, R2.1
DRV3: JP1.4, R3.1
GND: JP1.1, LEDG.K (C), LEDR.K (C), LEDY.K (C)
unnamed: LEDR.A, R1.2
unnamed: LEDY.A, R2.2
unnamed: LEDG.A, R3.2

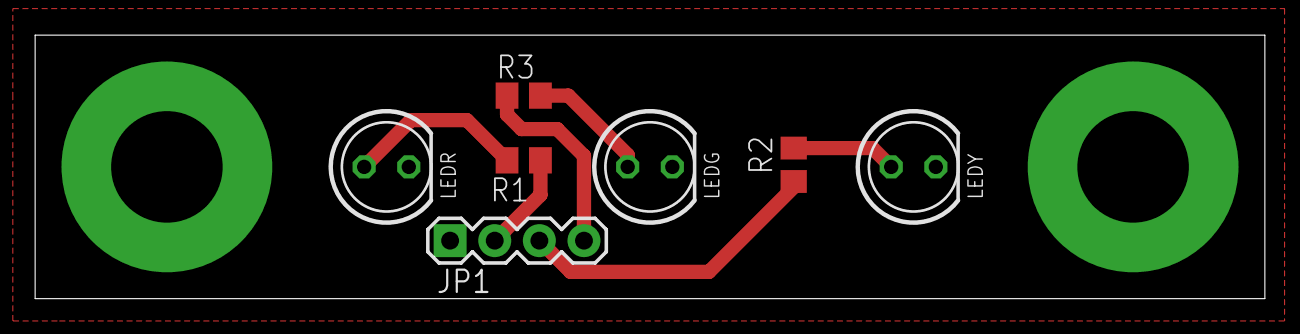
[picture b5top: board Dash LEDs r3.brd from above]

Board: 2 copper layers, 70.0 x 15.0 mm, 7 parts (0 on the bottom side), 7 nets.
